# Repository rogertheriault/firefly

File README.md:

# firefly
An annoying little thing, really

Here's a tiny pcb that you can stash somewhere and annoy people. Where's that chirping coming from?

It uses an LED, piezo buzzer, ATTINY13 Atmel microcontroller, a very small amount of Arduino code, and a coin cell battery that should last about a week.

Battery life could be improved, with longer sleep times.

The device has but one function: sleep, then wake up periodically and blink and chirp, then go back to sleep.

You can program the chip using a pogo pin programmer, like [this one from Sparkfun](https://learn.sparkfun.com/tutorials/tiny-avr-programmer-hookup-guide/programming-in-arduino)

### schematic

### parts
Board ID | Part Number | Description | Sources
--- | --- | --- | ---
IC1 | ATTINY13A-SU | SMT Atmel Attiny 13a | Mouser
LED1 | HT-121UYG-4739 | 0603 20ma bright yellow SMT LED | Mouser
SG1 | PKMCS0909E4000-R1 | 9MM square 4KHz piezo buzzer, SMT | Mouser
R1 | 1M   | 0603 1 Meg ohm SMT resistor | Mouser, Newark, Digikey
R2 | 1300 | 1206 1.3K ohm SMT resistor | Mouser, Newark, Digikey
CR-2032 | CR-2032 | 3.3v lithium battery | Mouser, Amazon
Holder |  BAT-HLD-001 | SMT battery holder | Mouser

### PCB

Eagle CAD files are in /board in case you want to iterate

You can also [order these from OshPark](https://oshpark.com/shared_projects/t0UHeqNX)

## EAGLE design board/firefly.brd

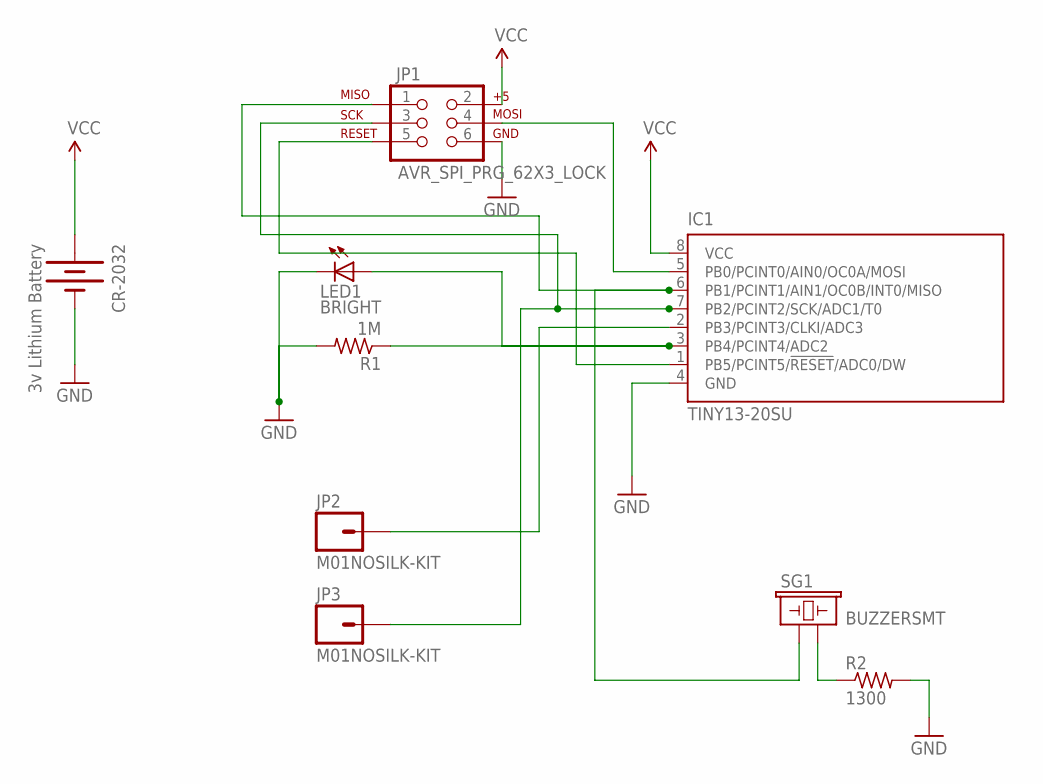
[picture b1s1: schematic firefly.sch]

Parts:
CR-2032: 3v Lithium Battery; BATTCON_20MM_4LEGS
IC1: TINY13-20SU; 8S2
JP1: AVR_SPI_PRG_62X3_LOCK; 2X3_LOCK
JP2, JP3: M01NOSILK-KIT; 1X01NS-KIT
LED1: BRIGHT; CHIP-LED0603
R1: 1M; R0603
R2: 1300; R1206
SG1: BUZZERSMT; BUZZER-9MM

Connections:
GND: CR-2032.2 (-), IC1.4 (GND), JP1.6, LED1.C, R1.2, R2.2
unnamed: IC1.3 (PB4/PCINT4/ADC2), LED1.A, R1.1
unnamed: IC1.1 (PB5/PCINT5/!RESET!/ADC0/DW), JP1.5
unnamed: IC1.7 (PB2/PCINT2/SCK/ADC1/T0), JP1.3, JP3.1
unnamed: IC1.6 (PB1/PCINT1/AIN1/OC0B/INT0/MISO), JP1.1, SG1.1
unnamed: IC1.5 (PB0/PCINT0/AIN0/OC0A/MOSI), JP1.4
unnamed: IC1.2 (PB3/PCINT3/CLKI/ADC3), JP2.1
unnamed: R2.1, SG1.2
VCC: CR-2032.1 (+), IC1.8 (VCC), JP1.2

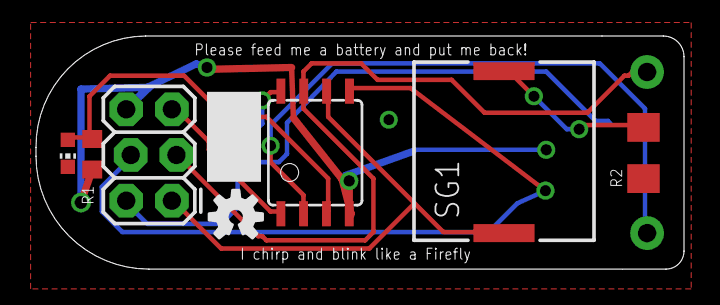
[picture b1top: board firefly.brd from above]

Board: 2 copper layers, 36.0 x 12.9 mm, 10 parts (1 on the bottom side), 9 nets.

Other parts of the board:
U$1: OSHW-LOGO-S

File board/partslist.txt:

Parts

ID       MFR Part

CR-2032  3.3v Lithium Battery  
Holder   BAT-HLD-001 (Mouser stocks)
IC1      ATTINY13A-SU          SMT  Atmel Attiny 13
LED1     HT-121UYG-4739        0603 20ma bright yellow LED
R1       1M                    0603
R2       1300                  1206
SG1      PKMCS0909E4000-R1     9MM square 4KHz Piezo buzzer

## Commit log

2018-02-02 Mostly complete project and readme, could use more instructions
2018-02-02 Eagle Cad board files and arduino code
2018-02-02 flipped bottom board face
2018-02-03 Added parts list and OshPark link to order boards
2018-02-03 pipe not bang

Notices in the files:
parts and their libraries:
SparkFun-Electromechanical: Licensing: Creative Commons ShareAlike 4.0 International - https://creativecommons.org/licenses/by-sa/4.0
